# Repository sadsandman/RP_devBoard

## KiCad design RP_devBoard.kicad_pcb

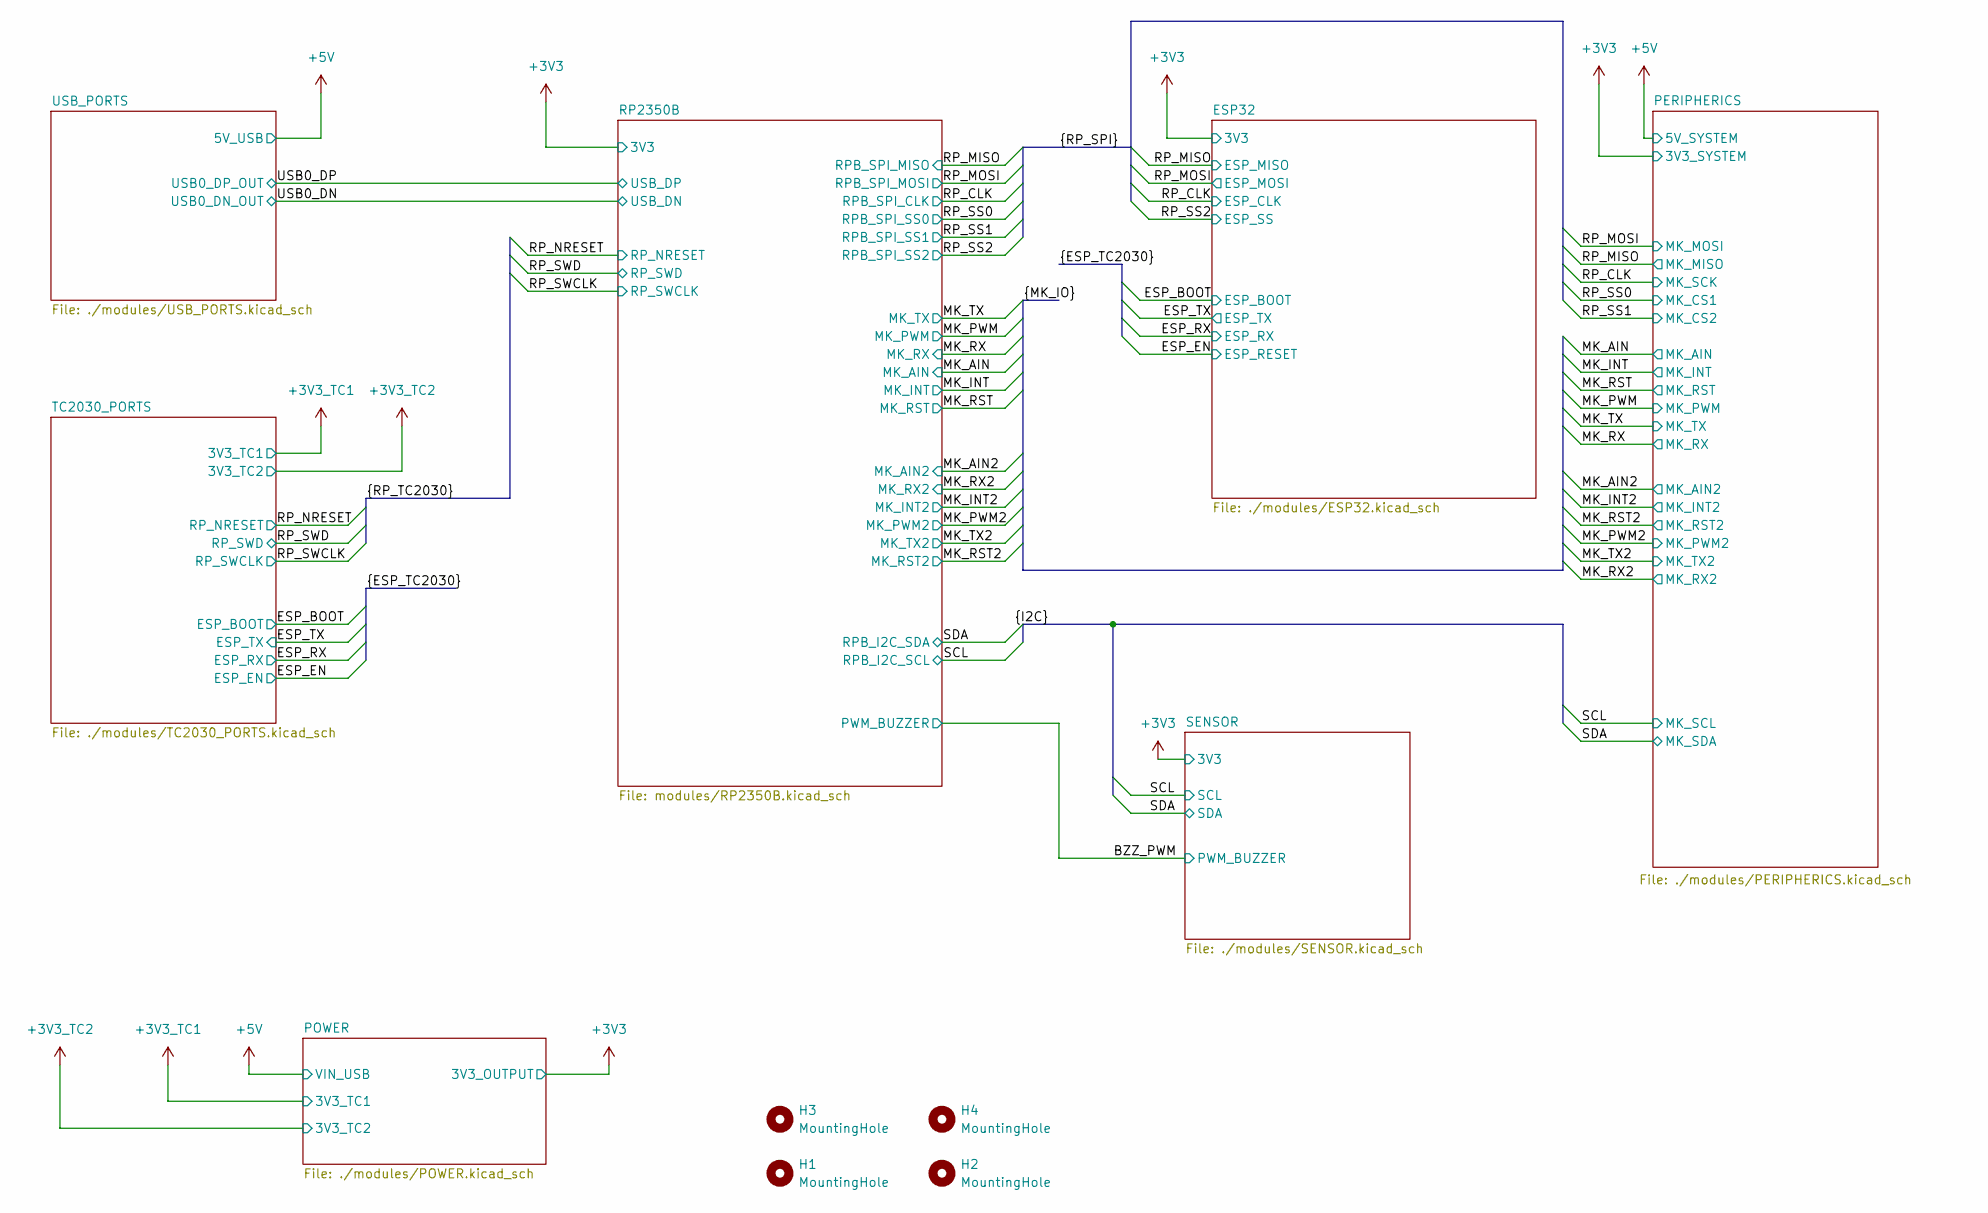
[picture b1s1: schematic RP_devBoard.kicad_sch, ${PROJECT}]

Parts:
H1, H2, H3, H4: MountingHole; MountingHole_3.2mm_M3_DIN965_Pad

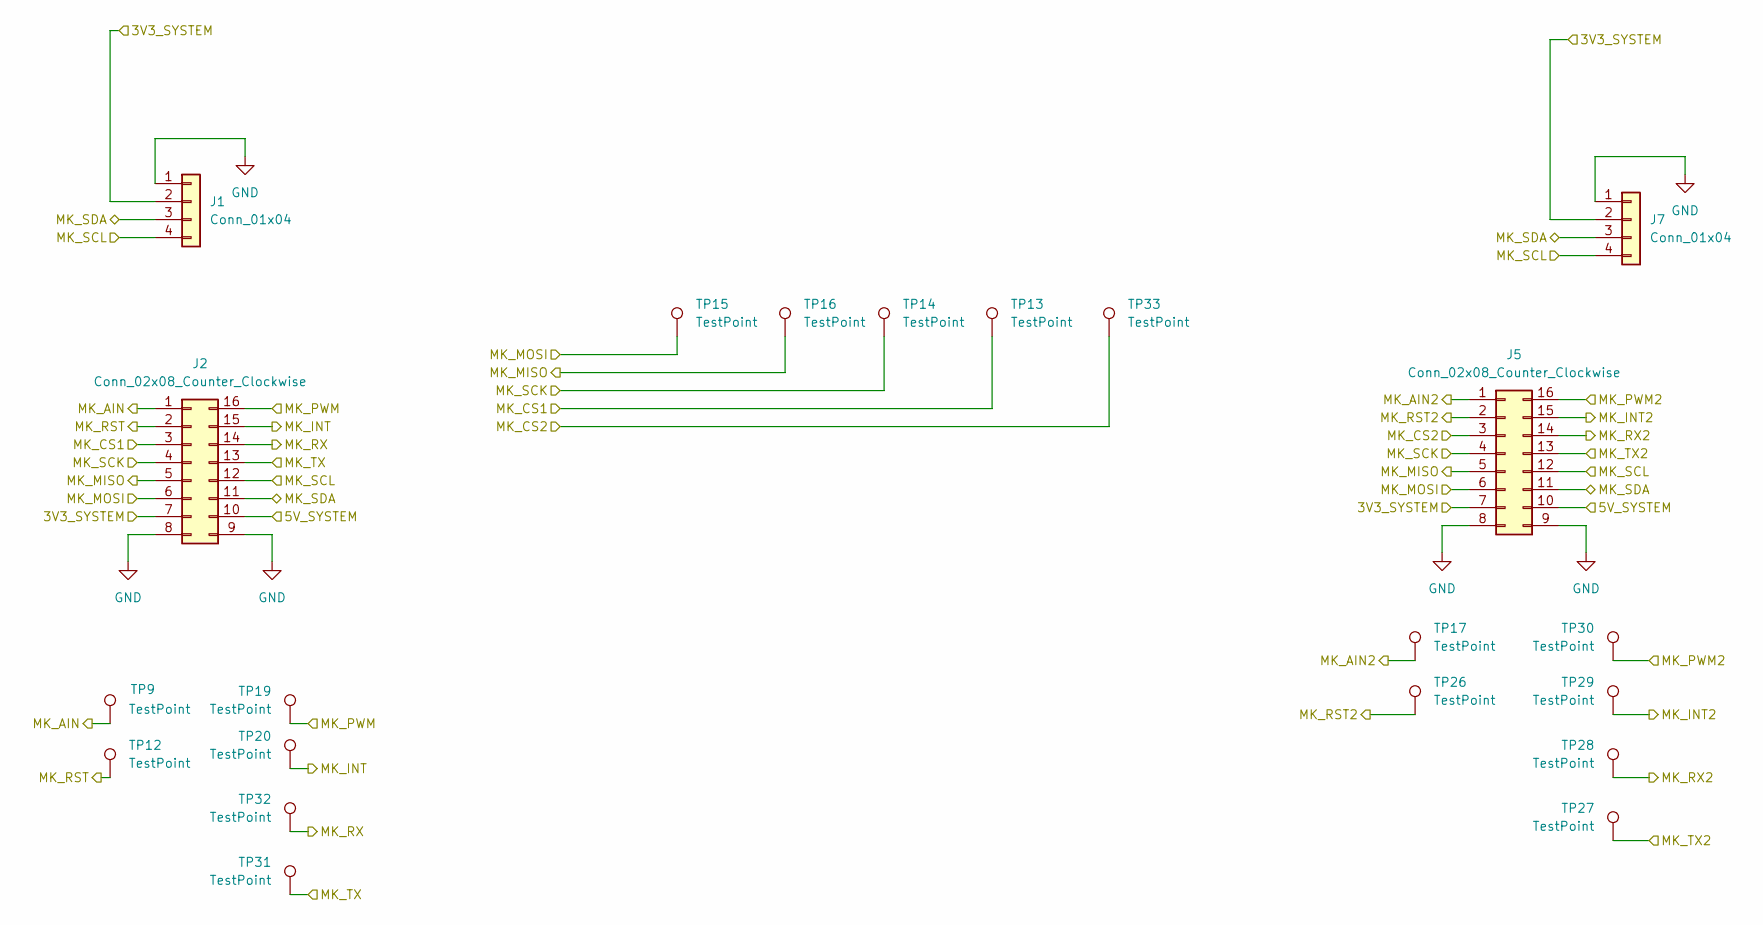
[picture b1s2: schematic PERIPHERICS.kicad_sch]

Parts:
J1, J7: Conn_01x04; JST_SH_SM04B-SRSS-TB_1x04-1MP_P1.00mm_Horizontal; Part Number SM04B-SRSS-TB
J2, J5: Conn_02x08_Counter_Clockwise; CONN2X8_MIKROE-4248_MKE; Part Number MIKROE-4248
TP9, TP12, TP13, TP14, TP15, TP16, TP17, TP19, TP20, TP26, TP27, TP28, TP29, TP30, TP31, TP32, TP33: TestPoint; TP_2.8mm_1mm

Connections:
+3V3: J1.2, J2.7, J5.7, J7.2; also elsewhere on the board
+5V: J2.10, J5.10; also elsewhere on the board
/MK_AIN: J2.1, TP9.1; also elsewhere on the board
/MK_AIN2: J5.1, TP17.1; also elsewhere on the board
/MK_INT: J2.15, TP20.1; also elsewhere on the board
/MK_INT2: J5.15, TP29.1; also elsewhere on the board
/MK_PWM: J2.16, TP19.1; also elsewhere on the board
/MK_PWM2: J5.16, TP30.1; also elsewhere on the board
/MK_RST: J2.2, TP12.1; also elsewhere on the board
/MK_RST2: J5.2, TP26.1; also elsewhere on the board
/MK_RX: J2.14, TP32.1; also elsewhere on the board
/MK_RX2: J5.14, TP28.1; also elsewhere on the board
/MK_TX: J2.13, TP31.1; also elsewhere on the board
/MK_TX2: J5.13, TP27.1; also elsewhere on the board
/RP_CLK: J2.4, J5.4, TP14.1; also elsewhere on the board
/RP_MISO: J2.5, J5.5, TP16.1; also elsewhere on the board
/RP_MOSI: J2.6, J5.6, TP15.1; also elsewhere on the board
/RP_SS0: J2.3, TP13.1; also elsewhere on the board
/RP_SS1: J5.3, TP33.1; also elsewhere on the board
/SCL: J1.4, J2.12, J5.12, J7.4; also elsewhere on the board
/SDA: J1.3, J2.11, J5.11, J7.3; also elsewhere on the board
GND: J1.1, J2.8, J2.9, J5.8, J5.9, J7.1; also elsewhere on the board

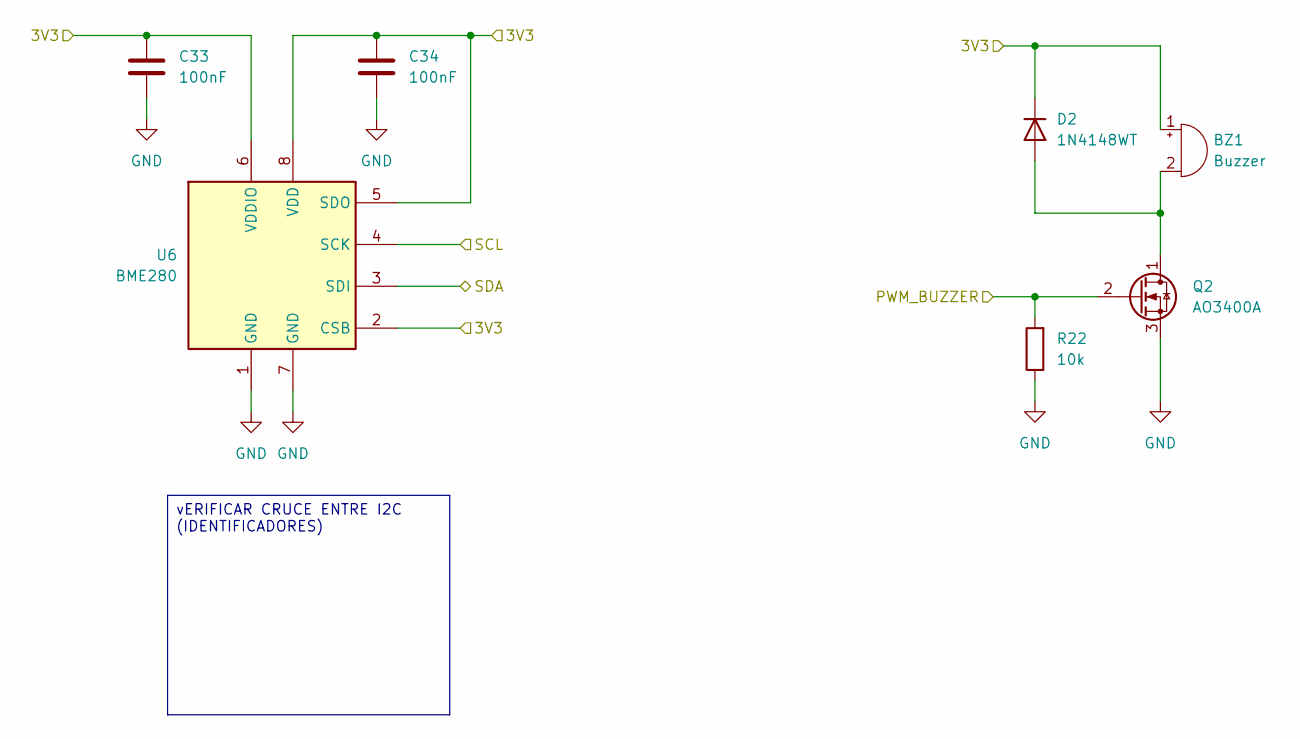
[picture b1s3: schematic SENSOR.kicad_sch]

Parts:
BZ1: Buzzer; SMT-0827-S-HT-R; Part Number SMT-0827-S-HT-R
C33, C34: 100nF; C_0402_1005Metric; Part Number CL05B104KA5NNNC
D2: 1N4148WT; D_SOD-523; Part Number 1N4148WT
Q2: AO3400A; SOT-23; Part Number AO3400A
R22: 10k; R_0603_1608Metric; Part Number RC0603FR-0710KL
U6: BME280; Bosch_LGA-8_2.5x2.5mm_P0.65mm_ClockwisePinNumbering; Part Number BME280

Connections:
+3V3: BZ1.1 (+), C33.1, C34.1, D2.1 (K), U6.2 (CSB), U6.5 (SDO), U6.6 (VDDIO), U6.8 (VDD); also elsewhere on the board
/BZZ_PWM: Q2.2 (G), R22.2; also elsewhere on the board
/SCL: U6.4 (SCK); also elsewhere on the board
/SDA: U6.3 (SDI); also elsewhere on the board
GND: C33.2, C34.2, Q2.3 (S), R22.1, U6.1 (GND), U6.7 (GND); also elsewhere on the board
unnamed: BZ1.2 (-), D2.2 (A), Q2.1 (D)

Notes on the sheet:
vERIFICAR CRUCE ENTRE I2C (IDENTIFICADORES)

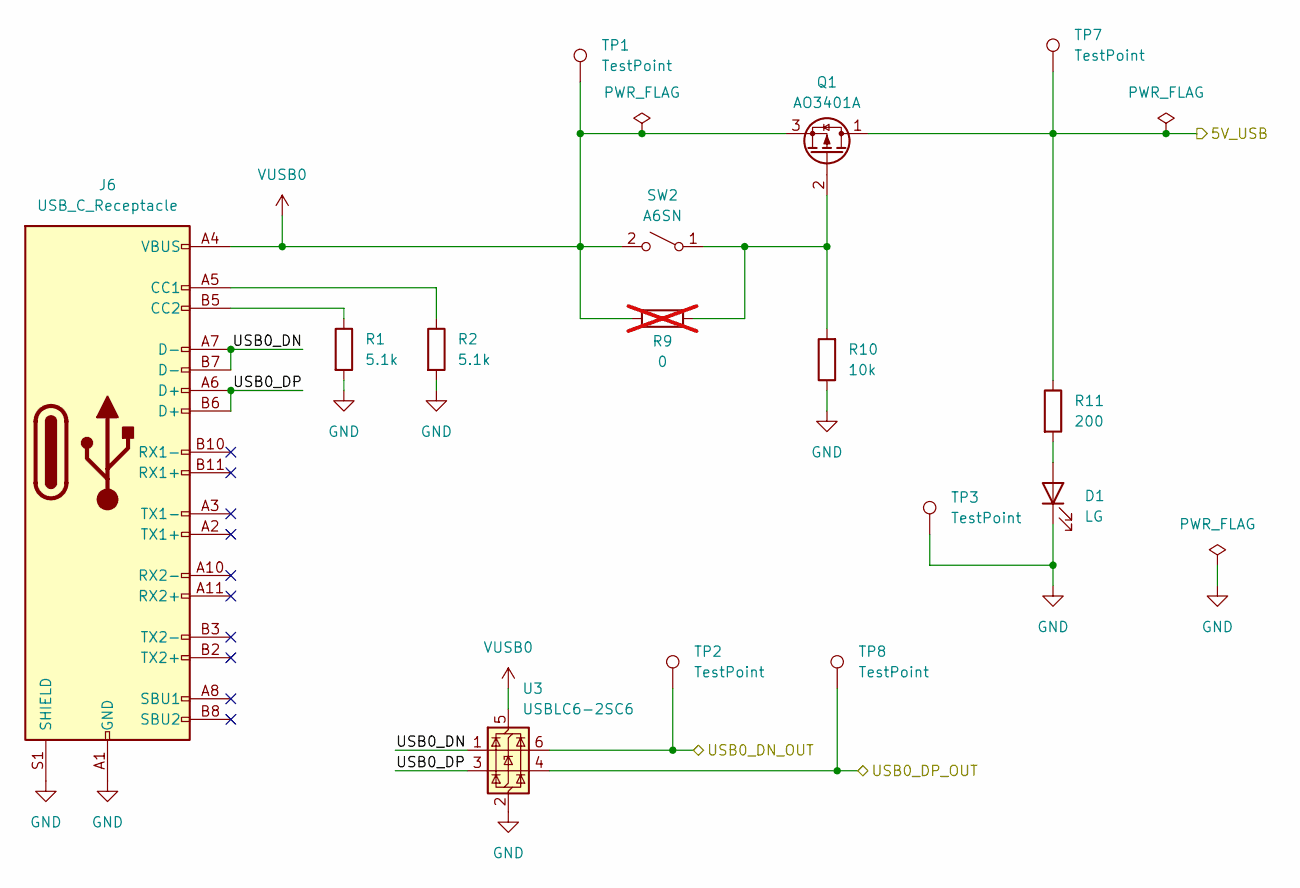
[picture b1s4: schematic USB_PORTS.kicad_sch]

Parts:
D1: LG; LED_0805_2012Metric; Part Number LG R971-KN-1-0-20-R18
J6: USB_C_Receptacle; USB_C_Receptacle_GCT_USB4105-xx-A_16P_TopMnt_Horizontal; Part Number USB4105-GF-A-120
Q1: AO3401A; SOT-23; Part Number AO3401A
R1, R2: 5.1k; R_0603_1608Metric; Part Number RC0603FR-075K1L
R9: 0; R_0805_2012Metric; not fitted
R10: 10k; R_0603_1608Metric; Part Number RC0603FR-0710KL
R11: 200; R_0805_2012Metric; Part Number ERJ-P06F2000V
SW2: A6SN; SW_DIP_SPSTx01_Slide_6.7x4.1mm_W6.73mm_P2.54mm_LowProfile_J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; Part Number A6SN-1101
TP1, TP2, TP3, TP7, TP8: TestPoint; TP_2.8mm_1mm
U3: USBLC6-2SC6; SOT-23-6; Part Number USBLC6-2SC6

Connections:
+5V: Q1.1 (D), R11.1, TP7.1; also elsewhere on the board
/USB0_DN: TP2.1, U3.6 (I/O1); also elsewhere on the board
/USB0_DP: TP8.1, U3.4 (I/O2); also elsewhere on the board
/USB_PORTS/USB0_DN: J6.A7 (D-), J6.B7 (D-), U3.1 (I/O1)
/USB_PORTS/USB0_DP: J6.A6 (D+), J6.B6 (D+), U3.3 (I/O2)
GND: D1.1 (K), J6.A1 (GND), J6.A12 (GND), J6.B1 (GND), J6.B12 (GND), J6.S1 (SHIELD), R1.2, R2.2, R10.1, TP3.1, U3.2 (GND); also elsewhere on the board
unnamed: D1.2 (A), R11.2
unnamed: J6.A5 (CC1), R2.1
unnamed: J6.B5 (CC2), R1.1
unnamed: Q1.2 (G), R9.2, R10.2, SW2.1 (A)
VUSB0: J6.A4 (VBUS), J6.A9 (VBUS), J6.B4 (VBUS), J6.B9 (VBUS), Q1.3 (S), R9.1, SW2.2 (B), TP1.1, U3.5 (VBUS)

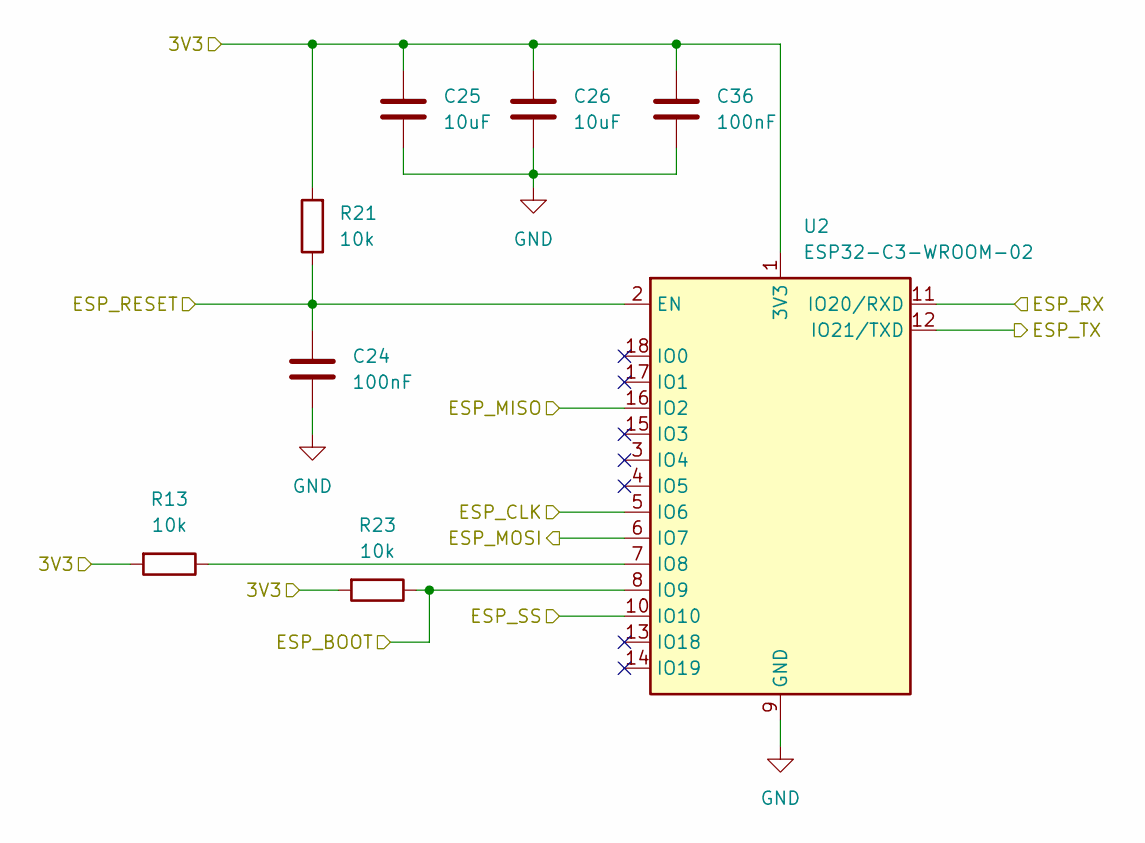
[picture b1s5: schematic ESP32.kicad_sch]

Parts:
C24, C36: 100nF; C_0603_1608Metric; Part Number C0603C104K5RACTU
C25, C26: 10uF; C_0603_1608Metric; Part Number CL10A106KP8NNNC
R13, R21, R23: 10k; R_0603_1608Metric; Part Number RC0603FR-0710KL
U2: ESP32-C3-WROOM-02; Part Number ESP32-C3-WROOM-02-H4

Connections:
+3V3: C25.1, C26.1, C36.1, R13.2, R21.2, R23.2, U2.1 (3V3); also elsewhere on the board
/ESP_BOOT: R23.1, U2.8 (IO9); also elsewhere on the board
/ESP_EN: C24.1, R21.1, U2.2 (EN); also elsewhere on the board
/ESP_RX: U2.11 (IO20/RXD); also elsewhere on the board
/ESP_TX: U2.12 (IO21/TXD); also elsewhere on the board
/RP_CLK: U2.5 (IO6); also elsewhere on the board
/RP_MISO: U2.16 (IO2); also elsewhere on the board
/RP_MOSI: U2.6 (IO7); also elsewhere on the board
/RP_SS2: U2.10 (IO10); also elsewhere on the board
GND: C24.2, C25.2, C26.2, C36.2, U2.9 (GND), U2.19 (GND); also elsewhere on the board
unnamed: R13.1, U2.7 (IO8)

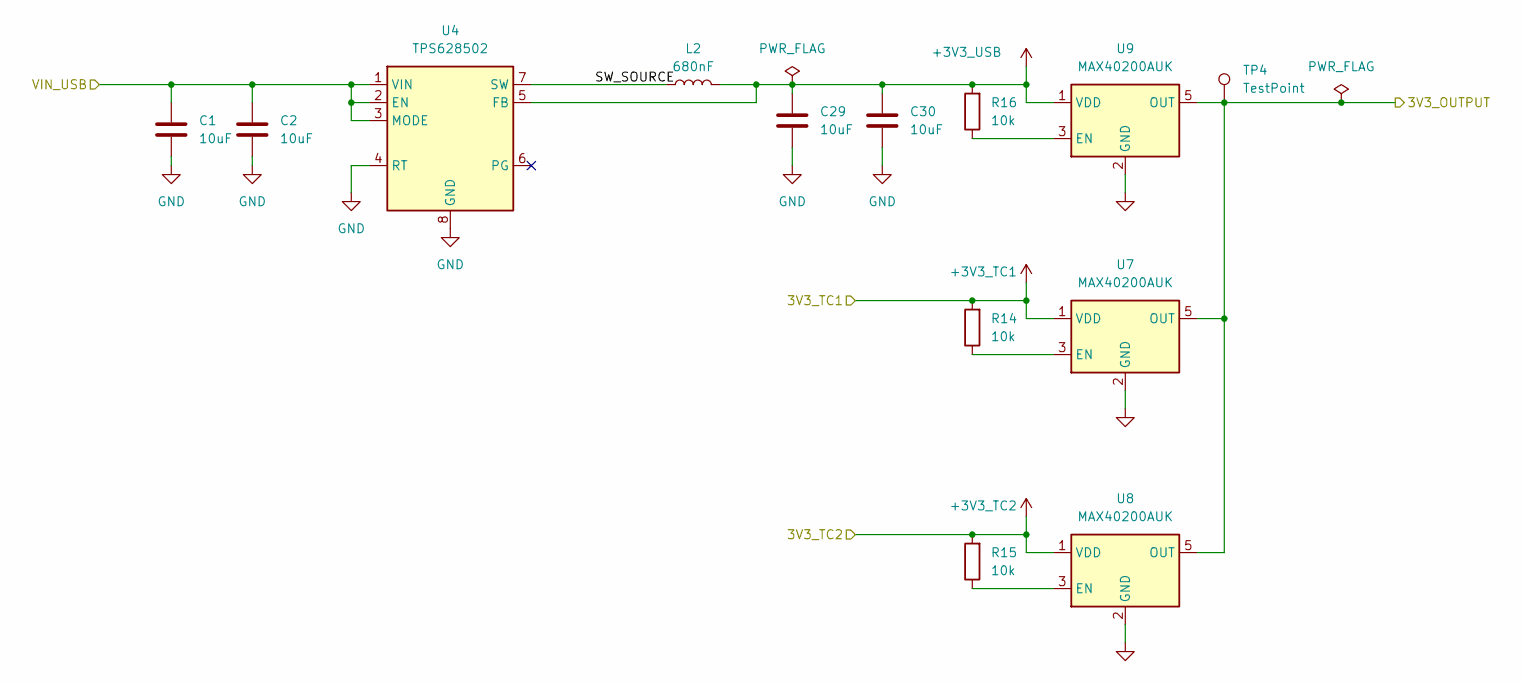
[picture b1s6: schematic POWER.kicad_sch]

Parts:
C1, C2, C29, C30: 10uF; C_0603_1608Metric; Part Number CL10A106KP8NNNC
L2: 680nF; L_1212_3030Metric; Part Number XFL3012-681MEC
R14, R15, R16: 10k; R_0603_1608Metric; Part Number RC0603FR-0710KL
TP4: TestPoint; TP_2.8mm_1mm
U4: TPS628502; SOT-583-8; Part Number TPS6285021HQDRLRQ1
U7, U8, U9: MAX40200AUK; SOT-23-5; Part Number MAX40200AUK+T

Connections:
+3V3: TP4.1, U7.5 (OUT), U8.5 (OUT), U9.5 (OUT); also elsewhere on the board
+3V3_TC1: R14.2, U7.1 (VDD); also elsewhere on the board
+3V3_TC2: R15.2, U8.1 (VDD); also elsewhere on the board
+3V3_USB: C29.1, C30.1, L2.2, R16.2, U4.5 (FB), U9.1 (VDD)
+5V: C1.1, C2.1, U4.1 (VIN), U4.2 (EN), U4.3 (MODE); also elsewhere on the board
/POWER/SW_SOURCE: L2.1, U4.7 (SW)
GND: C1.2, C2.2, C29.2, C30.2, U4.4 (RT), U4.8 (GND), U7.2 (GND), U8.2 (GND), U9.2 (GND); also elsewhere on the board
unnamed: R14.1, U7.3 (EN)
unnamed: R15.1, U8.3 (EN)
unnamed: R16.1, U9.3 (EN)

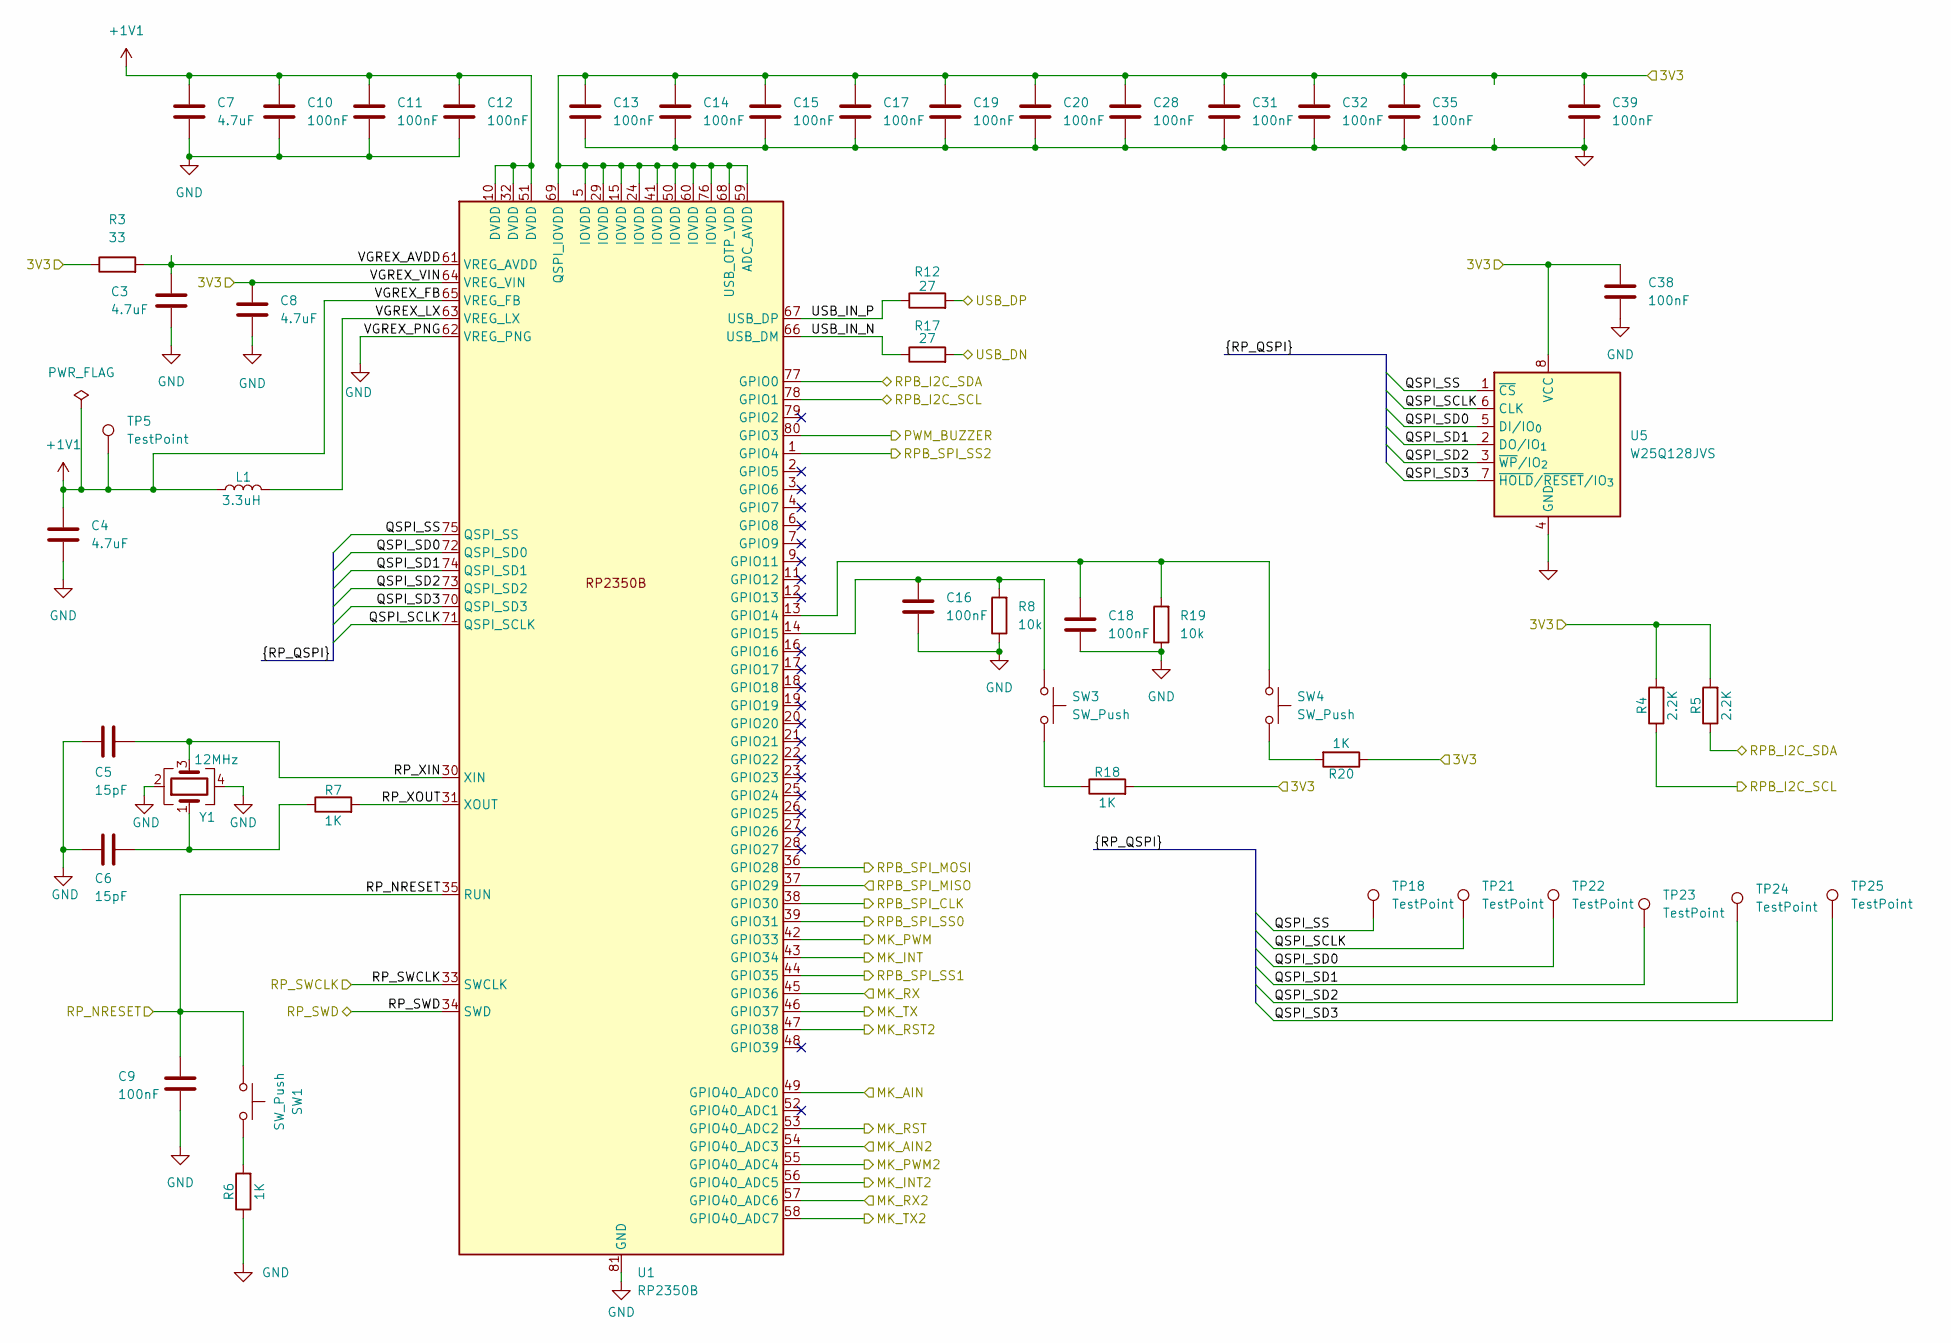
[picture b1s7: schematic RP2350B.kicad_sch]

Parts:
C3, C7: 4.7uF; C_0402_1005Metric; Part Number GRM155D71A475ME15J
C4, C8: 4.7uF; C_0603_1608Metric; Part Number GRM188R61E475KE11D
C5, C6: 15pF; C_0402_1005Metric; Part Number GJM1555C1H150FB01D
C9, C16, C18, C38: 100nF; C_0603_1608Metric; Part Number C0603C104K5RACTU
C10, C11, C12, C13, C14, C15, C17, C19, C20, C28, C31, C32, C35, C39: 100nF; C_0402_1005Metric; Part Number CL05B104KA5NNNC
L1: 3.3uH; L_0806_2016Metric; Part Number AOTA-B201610S3R3-101-T
R3: 33; R_0402_1005Metric; Part Number RC0402JR-0733RL
R4, R5: 2.2K; R_0603_1608Metric; Part Number RC0603FR-072K2L
R6, R18, R20: 1K; R_0603_1608Metric; Part Number RMCF0603FT1K00
R7: 1K; R_0402_1005Metric; Part Number ERJ-2RKF1001X
R8, R19: 10k; R_0603_1608Metric; Part Number RC0603FR-0710KL
R12, R17: 27; R_0402_1005Metric; Part Number RC0402FR-0727RL
SW1, SW3, SW4: SW_Push; SW_Push_1P1T_NO_Vertical_Wuerth_434133025816; Part Number 434133025816
TP5, TP18, TP21, TP22, TP23, TP24, TP25: TestPoint; TP_2.8mm_1mm
U1: RP2350B; QFN-80-1EP_10x10mm_P0.4mm_EP3.4x3.4mm; Part Number SC1510-A4
U5: W25Q128JVS; SOIC-8_5.3x5.3mm_P1.27mm; Part Number W25Q128JVSIM TR
Y1: 12MHz; Crystal_SMD_3225-4Pin_3.2x2.5mm; Part Number ABM8-272-T3

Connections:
+1V1: C4.1, C7.1, C10.1, C11.1, C12.1, L1.1, TP5.1, U1.10 (DVDD), U1.32 (DVDD), U1.51 (DVDD), U1.65 (VREG_FB)
+3V3: C8.1, C13.1, C14.1, C15.1, C17.1, C19.1, C20.1, C28.1, C31.1, C32.1, C35.1, C38.1, C39.1, R3.1, R4.2, R5.2, R18.2, R20.1, U1.5 (IOVDD), U1.15 (IOVDD), U1.24 (IOVDD), U1.29 (IOVDD), U1.41 (IOVDD), U1.50 (IOVDD), U1.59 (ADC_AVDD), U1.60 (IOVDD), U1.64 (VREG_VIN), U1.68 (USB_OTP_VDD), U1.69 (QSPI_IOVDD), U1.76 (IOVDD), U5.8 (VCC); also elsewhere on the board
/BZZ_PWM: U1.80 (GPIO3); also elsewhere on the board
/MK_AIN: U1.49 (GPIO40_ADC0); also elsewhere on the board
/MK_AIN2: U1.54 (GPIO40_ADC3); also elsewhere on the board
/MK_INT: U1.43 (GPIO34); also elsewhere on the board
/MK_INT2: U1.56 (GPIO40_ADC5); also elsewhere on the board
/MK_PWM: U1.42 (GPIO33); also elsewhere on the board
/MK_PWM2: U1.55 (GPIO40_ADC4); also elsewhere on the board
/MK_RST: U1.53 (GPIO40_ADC2); also elsewhere on the board
/MK_RST2: U1.47 (GPIO38); also elsewhere on the board
/MK_RX: U1.45 (GPIO36); also elsewhere on the board
/MK_RX2: U1.57 (GPIO40_ADC6); also elsewhere on the board
/MK_TX: U1.46 (GPIO37); also elsewhere on the board
/MK_TX2: U1.58 (GPIO40_ADC7); also elsewhere on the board
/RP2350B/QSPI_SCLK: TP21.1, U1.71 (QSPI_SCLK), U5.6 (CLK)
/RP2350B/QSPI_SD0: TP22.1, U1.72 (QSPI_SD0), U5.5 (DI/IO_{0})
/RP2350B/QSPI_SD1: TP23.1, U1.74 (QSPI_SD1), U5.2 (DO/IO_{1})
/RP2350B/QSPI_SD2: TP24.1, U1.73 (QSPI_SD2), U5.3 (~WP/IO_{2})
/RP2350B/QSPI_SD3: TP25.1, U1.70 (QSPI_SD3), U5.7 (~HOLD/~RESET/IO_{3})
/RP2350B/QSPI_SS: TP18.1, U1.75 (QSPI_SS), U5.1 (~CS)
/RP2350B/RP_XIN: C5.1, U1.30 (XIN), Y1.3
/RP2350B/RP_XOUT: R7.2, U1.31 (XOUT)
/RP2350B/USB_IN_N: R17.1, U1.66 (USB_DM)
/RP2350B/USB_IN_P: R12.1, U1.67 (USB_DP)
/RP2350B/VGREX_AVDD: C3.1, R3.2, U1.61 (VREG_AVDD)
/RP2350B/VGREX_LX: L1.2, U1.63 (VREG_LX)
/RP_CLK: U1.38 (GPIO30); also elsewhere on the board
/RP_MISO: U1.37 (GPIO29); also elsewhere on the board
/RP_MOSI: U1.36 (GPIO28); also elsewhere on the board
/RP_NRESET: C9.1, SW1.2, U1.35 (RUN); also elsewhere on the board
/RP_SS0: U1.39 (GPIO31); also elsewhere on the board
/RP_SS1: U1.44 (GPIO35); also elsewhere on the board
/RP_SS2: U1.1 (GPIO4); also elsewhere on the board
/RP_SWCLK: U1.33 (SWCLK); also elsewhere on the board
/RP_SWD: U1.34 (SWD); also elsewhere on the board
/SCL: R4.1, U1.78 (GPIO1); also elsewhere on the board
/SDA: R5.1, U1.77 (GPIO0); also elsewhere on the board
/USB0_DN: R17.2; also elsewhere on the board
/USB0_DP: R12.2; also elsewhere on the board
GND: C3.2, C4.2, C5.2, C6.2, C7.2, C8.2, C9.2, C10.2, C11.2, C12.2, C13.2, C14.2, C15.2, C16.2, C17.2, C18.2, C19.2, C20.2, C28.2, C31.2, C32.2, C35.2, C38.2, C39.2, R6.1, R8.1, R19.1, U1.62 (VREG_PNG), U1.81 (GND), U5.4 (GND), Y1.2, Y1.4; also elsewhere on the board
unnamed: C6.1, R7.1, Y1.1
unnamed: R6.2, SW1.1
unnamed: R18.1, SW3.2
unnamed: R20.2, SW4.2
unnamed: C18.1, R19.2, SW4.1, U1.13 (GPIO14)
unnamed: C16.1, R8.2, SW3.1, U1.14 (GPIO15)

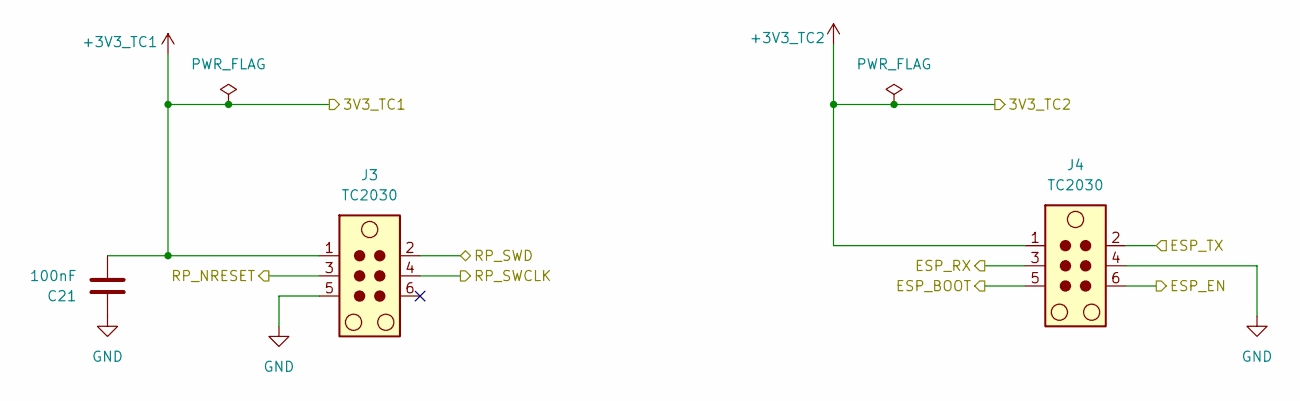
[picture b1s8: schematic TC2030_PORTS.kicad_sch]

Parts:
C21: 100nF; C_0402_1005Metric; Part Number CL05B104KA5NNNC
J3, J4: TC2030; Tag-Connect_TC2030-IDC-NL_2x03_P1.27mm_Vertical

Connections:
+3V3_TC1: C21.2, J3.1; also elsewhere on the board
+3V3_TC2: J4.1; also elsewhere on the board
/ESP_BOOT: J4.5; also elsewhere on the board
/ESP_EN: J4.6; also elsewhere on the board
/ESP_RX: J4.3; also elsewhere on the board
/ESP_TX: J4.2; also elsewhere on the board
/RP_NRESET: J3.3; also elsewhere on the board
/RP_SWCLK: J3.4; also elsewhere on the board
/RP_SWD: J3.2; also elsewhere on the board
GND: C21.1, J3.5, J4.4; also elsewhere on the board

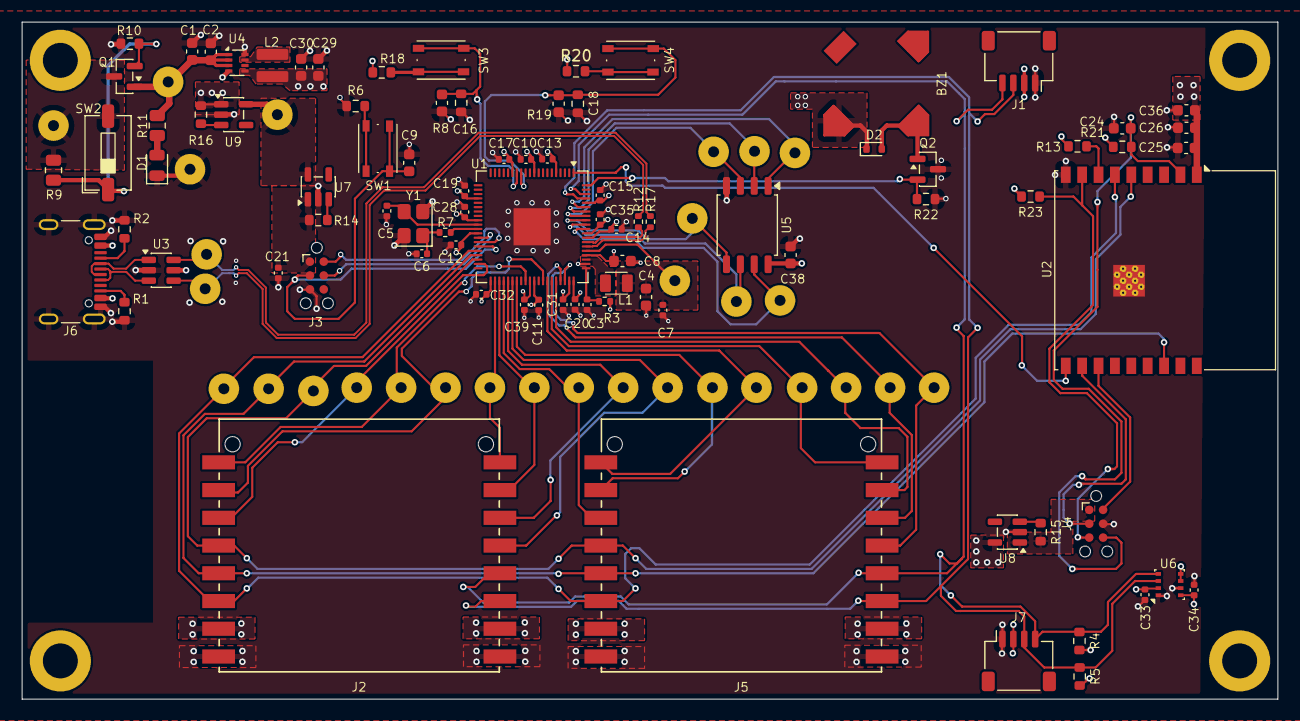
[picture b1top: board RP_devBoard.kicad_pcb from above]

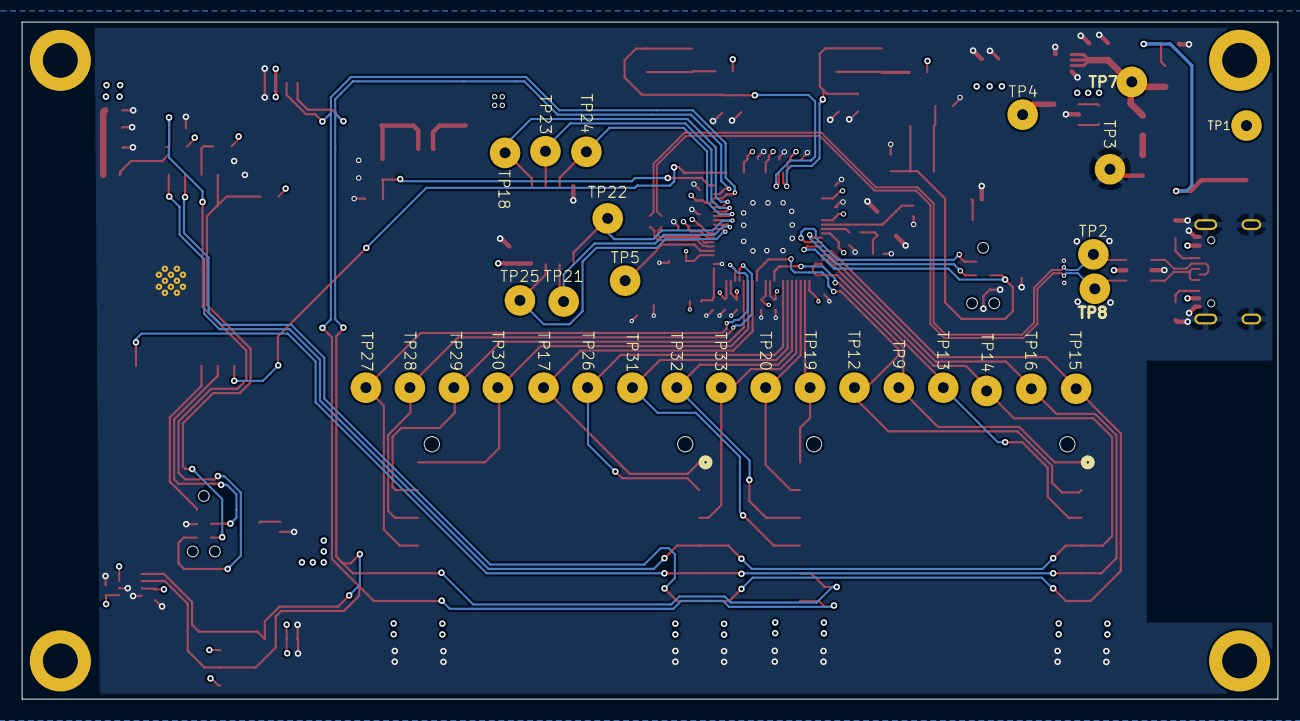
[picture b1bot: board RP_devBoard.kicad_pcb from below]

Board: 4 copper layers, 115.0 x 62.0 mm, 120 parts (30 on the bottom side), 68 nets.

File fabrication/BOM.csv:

"#","Reference","Description","Qty","Manufacturer","Mfg Part #","Footprint","Supplier","Value"
"1","BZ1","Buzzer, polarized","1","","","Sadman_audio:SMT-0827-S-HT-R","","Buzzer"
"2","C1,C2,C25,C26,C29,C30","CAP CER 10UF 10V X5R 0603","6","","","Capacitor_SMD:C_0603_1608Metric","","10uF"
"3","C3,C4,C7,C8","CAP CER 4.7UF 10V X7T 0402,CAP CER 4.7UF 25V X5R 0603","4","","","Capacitor_SMD:C_0402_1005Metric,Capacitor_SMD:C_0603_1608Metric","","4.7uF"
"4","C5,C6","CAP CER 15PF 50V C0G/NP0 0402","2","","","Capacitor_SMD:C_0402_1005Metric","","15pF"
"5","C9,C10,C11,C12,C13,C14,C15,C16,C17,C18,C19,C20,C21,C24,C28,C31,C32,C33,C34,C35,C36,C38,C39","CAP CER 0.1UF 25V X7R 0402,CAP CER 0.1UF 50V X7R 0603","23","","","Capacitor_SMD:C_0402_1005Metric,Capacitor_SMD:C_0603_1608Metric","","100nF"
"6","D1","LED GREEN DIFFUSED 0805 SMD","1","","","LED_SMD:LED_0805_2012Metric","","LG"
"7","D2","DIODE STANDARD 75V 200MA SOD523F","1","","","Diode_SMD:D_SOD-523","","1N4148WT"
"8","J6","https://gct.co/files/specs/usb4105-spec.pdf","1","","","Connector_USB:USB_C_Receptacle_GCT_USB4105-xx-A_16P_TopMnt_Horizontal","","USB_C_Receptacle"
"9","J1,J7","CONN HEADER SMD R/A 4POS 1MM","2","","","Connector_JST:JST_SH_SM04B-SRSS-TB_1x04-1MP_P1.00mm_Horizontal","","Conn_01x04"
"10","J2,J5","SOCKET MIKROBUS 16 SMD","2","","","Sadman_connectors:CONN2X8_MIKROE-4248_MKE","","Conn_02x08_Counter_Clockwise"
"11","L1","FIXED IND 3.3UH 2.1A 140 MOHM","1","","","sadman_power_passive:L_0806_2016Metric","","3.3uH"
"12","L2","FIXED IND 680NH 2.1A 40 MOHM SMD","1","","","sadman_power_passive:L_1212_3030Metric","","680nF"
"13","Q1","MOSFET P-CH 30V 4A SOT23-3L","1","","","Package_TO_SOT_SMD:SOT-23","","AO3401A"
"14","Q2","N-MOSFET transistor, drain/gate/source","1","","","Package_TO_SOT_SMD:SOT-23","","AO3400A"
"15","R3","RES 33 OHM 5% 1/16W 0402","1","","","Resistor_SMD:R_0402_1005Metric","","33"
"16","R11","RES SMD 200 OHM 1% 1/2W 0805","1","","","Resistor_SMD:R_0805_2012Metric","","200"
"17","R1,R2","RES 5.1K OHM 1% 1/10W 0603","2","","","Resistor_SMD:R_0603_1608Metric","","5.1k"
"18","R12,R17","RES 27 OHM 1% 1/16W 0402","2","","","Resistor_SMD:R_0402_1005Metric","","27"
"19","R4,R5","RES 2.2K OHM 1% 1/10W 0603","2","","","Resistor_SMD:R_0603_1608Metric","","2.2K"
"20","R6,R7,R18,R20","RES 1K OHM 1% 1/10W 0603,RES SMD 1K OHM 1% 1/10W 0402","4","","","Resistor_SMD:R_0402_1005Metric,Resistor_SMD:R_0603_1608Metric","","1K"
"21","R8,R10,R13,R14,R15,R16,R19,R21,R22,R23","RES 10K OHM 1% 1/10W 0603","10","","","Resistor_SMD:R_0603_1608Metric","","10k"
"22","SW2","SWITCH SLIDE DIP SPST 0.025A 24V","1","","","Button_Switch_SMD:SW_DIP_SPSTx01_Slide_6.7x4.1mm_W6.73mm_P2.54mm_LowProfile_JPin","","A6SN"
"23","SW1,SW3,SW4","SWITCH TACTILE SPST-NO 0.05A 16V","3","","","Button_Switch_SMD:SW_Push_1P1T_NO_Vertical_Wuerth_434133025816","","SW_Push"
"24","TP1,TP2,TP3,TP4,TP5,TP7,TP8,TP9,TP12,TP13,TP14,TP15,TP16,TP17,TP18,TP19,TP20,TP21,TP22,TP23,TP24,TP25,TP26,TP27,TP28,TP29,TP30,TP31,TP32,TP33","test point","30","","","Sadman_TP:TP_2.8mm_1mm","","TestPoint"
"25","U1","RP2350B / 7"" REEL - 500PCS","1","","","Package_DFN_QFN:QFN-80-1EP_10x10mm_P0.4mm_EP3.4x3.4mm","","RP2350B"
"26","U2","802.11 b/g/n Wi­Fi and Bluetooth 5 module, ESP32­C3 SoC, RISC­V microprocessor, On-board antenna","1","","","RF_Module:ESP32-C3-WROOM-02","","ESP32-C3-WROOM-02"
"27","U3","Very low capacitance ESD protection diode, 2 data-line, SOT-23-6","1","","","Package_TO_SOT_SMD:SOT-23-6","","USBLC6-2SC6"
"28","U4","IC REG BUCK 3.3V 2A SOT583","1","","","Package_TO_SOT_SMD:SOT-583-8","","TPS628502"
"29","U5","128Mbit / 16MiB Serial Flash Memory, Standard/Dual/Quad SPI, 2.7-3.6V, SOIC-8","1","","","Package_SO:SOIC-8_5.3x5.3mm_P1.27mm","","W25Q128JVS"
"30","U6","3-in-1 sensor, humidity, pressure, temperature, I2C and SPI interface, 1.71-3.6V, LGA-8","1","","","Package_LGA:Bosch_LGA-8_2.5x2.5mm_P0.65mm_ClockwisePinNumbering","","BME280"
"31","U7,U8,U9","IC DIODE CURRENT SWITCH SOT23-5","3","","","Package_TO_SOT_SMD:SOT-23-5","","MAX40200AUK"
"32","Y1","CRYSTAL 12.0000MHZ 10PF SMD","1","","","Crystal:Crystal_SMD_3225-4Pin_3.2x2.5mm","","12MHz"

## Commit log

2026-01-28 Adding RP And ESP configuration
2026-01-29 Adding source, source control
2026-01-30 Adding mikroBUS
2026-02-01 Modificaciond de conexiones
2026-02-02 correction of mikroBUS, USB on ESP32 and power mosfet
2026-02-09 pcb power layout
2026-02-15 save
2026-03-02 Cambio de layout, correccion de pinout
2026-03-09 finishing version 1.0
